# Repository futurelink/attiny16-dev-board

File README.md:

## Small ATTiny1616/3216 development board with built-in RS-485/USB

This board was designed to work with new AVR chips that were based on good old architecture.
These chips have one undisputable feature - they are in tiny packages (VQFN-20 is 4x4mm) 
and they are extremely cheap but can run at 20MHz and have a full bunch of peripheral inside.

I also placed MAX3485 to support RS-485 line which can be switched back to CH340G to connect it
via USB (or even both can be disconnected if not needed).

A few images below:

Dimansions are here:

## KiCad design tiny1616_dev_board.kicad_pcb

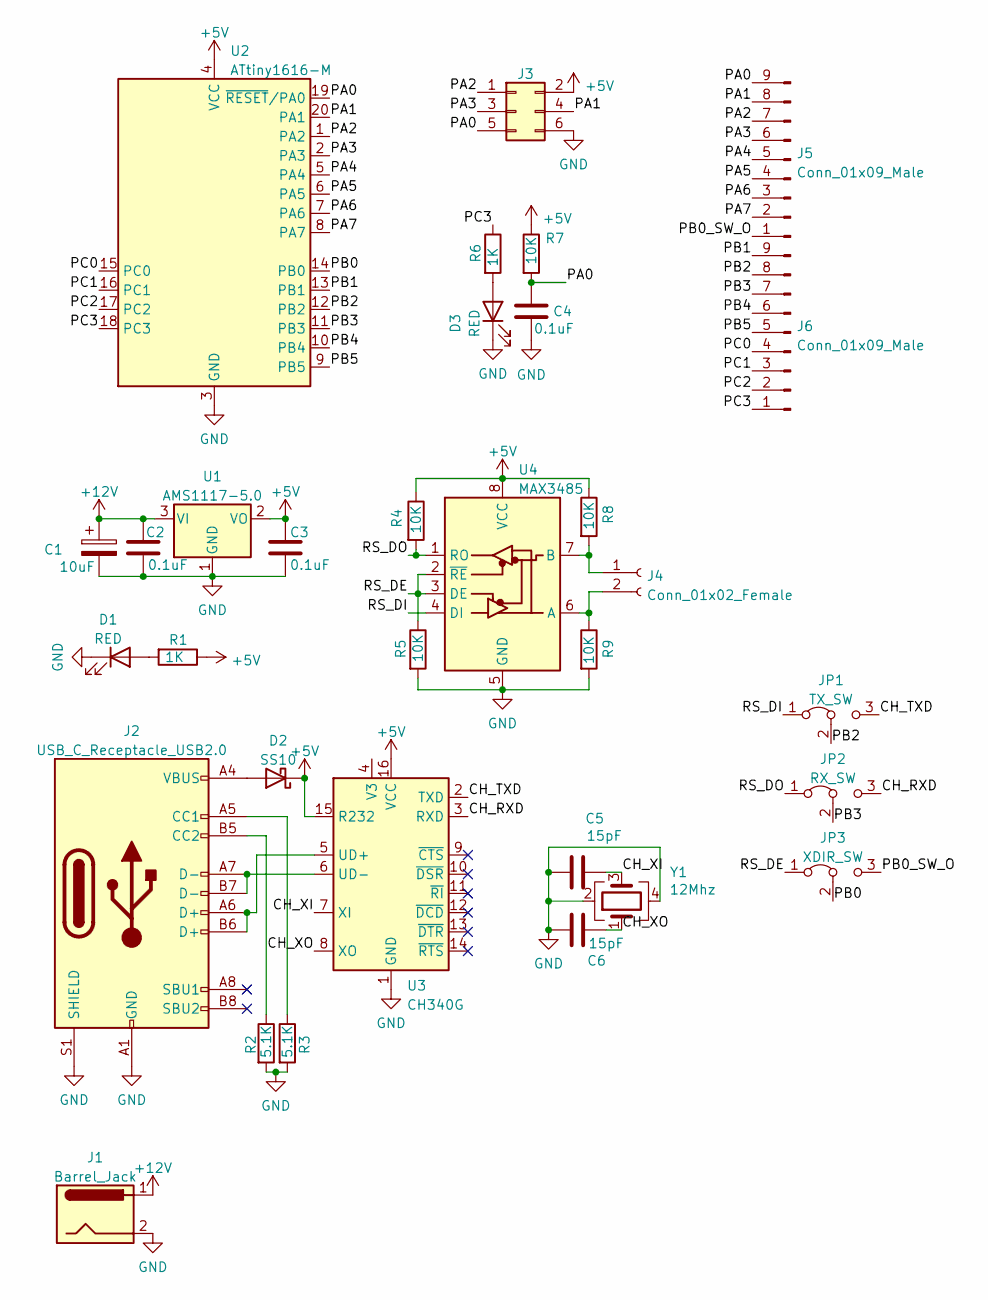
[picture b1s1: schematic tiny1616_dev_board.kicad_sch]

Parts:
C1: 10uF; CP_EIA-3216-10_Kemet-I
C2, C3, C4: 0.1uF; C_0603_1608Metric
C5, C6: 15pF; C_0603_1608Metric
D1, D3: RED; D_0603_1608Metric
D2: SS10; D_SOD-323
J1: Barrel_Jack; BarrelJack_Horizontal
J2: USB_C_Receptacle_USB2.0; USB_C_Receptacle_Palconn_UTC16-G
J3: Conn_02x03_Odd_Even; PinHeader_2x03_P2.54mm_Vertical
J4: Conn_01x02_Female; JST_EH_B2B-EH-A_1x02_P2.50mm_Vertical
J5, J6: Conn_01x09_Male; PinHeader_1x09_P2.54mm_Vertical
JP1: TX_SW; PinHeader_1x03_P2.54mm_Vertical
JP2: RX_SW; PinHeader_1x03_P2.54mm_Vertical
JP3: XDIR_SW; PinHeader_1x03_P2.54mm_Vertical
R1, R6: 1K; R_0603_1608Metric
R2, R3: 5.1K; R_0603_1608Metric
R4, R5, R7, R8, R9: 10K; R_0603_1608Metric
U1: AMS1117-5.0; SOT-223-3_TabPin2
U2: ATtiny1616-M; VQFN-20-1EP_3x3mm_P0.4mm_EP1.7x1.7mm
U3: CH340G; SOIC-16_3.9x9.9mm_P1.27mm
U4: MAX3485; SOIC-8_3.9x4.9mm_P1.27mm
Y1: 12Mhz; Crystal_SMD_3225-4Pin_3.2x2.5mm

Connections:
+5V: C3.1, D2.1 (K), J3.2, R1.1, R4.1, R7.1, R8.1, U1.2 (VO), U2.4 (VCC), U3.15 (R232), U3.16 (VCC), U4.8 (VCC)
+12V: C1.1, C2.1, J1.1, U1.3 (VI)
/CH_RXD: JP2.3 (B), U3.3 (RXD)
/CH_TXD: JP1.3 (B), U3.2 (TXD)
/CH_XI: C5.2, U3.7 (XI), Y1.3
/CH_XO: C6.2, U3.8 (XO), Y1.1
/PA0: C4.1, J3.5, J5.9, R7.2, U2.19 (~RESET/PA0)
/PA1: J3.4, J5.8, U2.20 (PA1)
/PA2: J3.1, J5.7, U2.1 (PA2)
/PA3: J3.3, J5.6, U2.2 (PA3)
/PA4: J5.5, U2.5 (PA4)
/PA5: J5.4, U2.6 (PA5)
/PA6: J5.3, U2.7 (PA6)
/PA7: J5.2, U2.8 (PA7)
/PB0: JP3.2 (C), U2.14 (PB0)
/PB0_SW_O: J5.1, JP3.3 (B)
/PB1: J6.9, U2.13 (PB1)
/PB2: J6.8, JP1.2 (C), U2.12 (PB2)
/PB3: J6.7, JP2.2 (C), U2.11 (PB3)
/PB4: J6.6, U2.10 (PB4)
/PB5: J6.5, U2.9 (PB5)
/PC0: J6.4, U2.15 (PC0)
/PC1: J6.3, U2.16 (PC1)
/PC2: J6.2, U2.17 (PC2)
/PC3: J6.1, R6.1, U2.18 (PC3)
/RS_DE: JP3.1 (A), R5.1, U4.2 (~RE), U4.3 (DE)
/RS_DI: JP1.1 (A), U4.4 (DI)
/RS_DO: JP2.1 (A), R4.2, U4.1 (RO)
GND: C1.2, C2.2, C3.2, C4.2, C5.1, C6.1, D1.1 (K), D3.1 (K), J1.2, J2.A1 (GND), J2.A12 (GND), J2.B1 (GND), J2.B12 (GND), J2.S1 (SHIELD), J3.6, R2.2, R3.2, R5.2, R9.2, U1.1 (GND), U2.3 (GND), U2.21 (GND), U3.1 (GND), U4.5 (GND), Y1.2, Y1.4
unnamed: D1.2 (A), R1.2
unnamed: D2.2 (A), J2.A4 (VBUS), J2.A9 (VBUS), J2.B4 (VBUS), J2.B9 (VBUS)
unnamed: D3.2 (A), R6.2
unnamed: J2.A5 (CC1), R3.1
unnamed: J2.A6 (D+), J2.B6 (D+), U3.5 (UD+)
unnamed: J2.A7 (D-), J2.B7 (D-), U3.6 (UD-)
unnamed: J2.B5 (CC2), R2.1
unnamed: J4.1, R8.2, U4.7 (B)
unnamed: J4.2, R9.1, U4.6 (A)

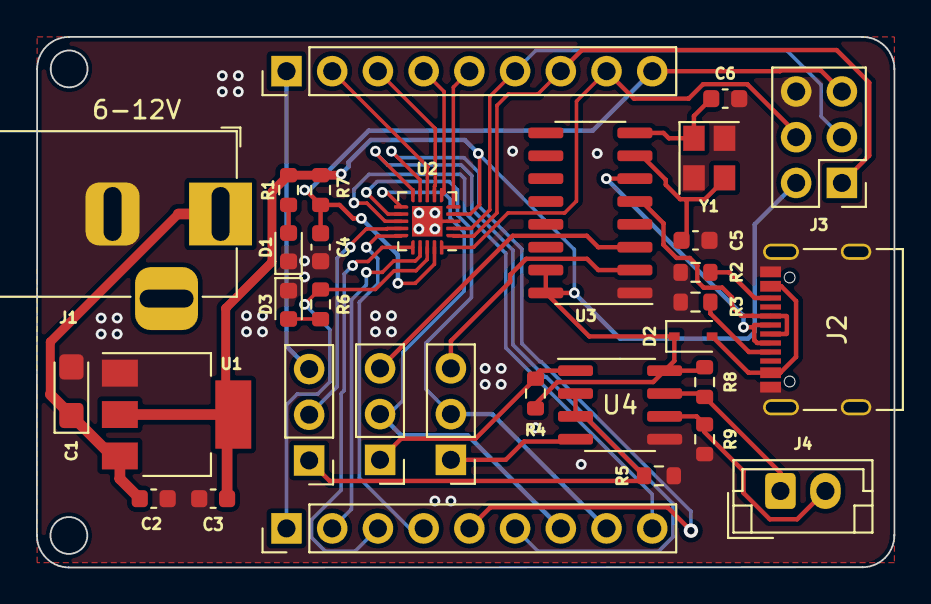
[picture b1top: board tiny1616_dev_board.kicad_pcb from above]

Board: 2 copper layers, 47.6 x 29.5 mm, 32 parts (0 on the bottom side), 38 nets.

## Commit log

2023-05-25 README
